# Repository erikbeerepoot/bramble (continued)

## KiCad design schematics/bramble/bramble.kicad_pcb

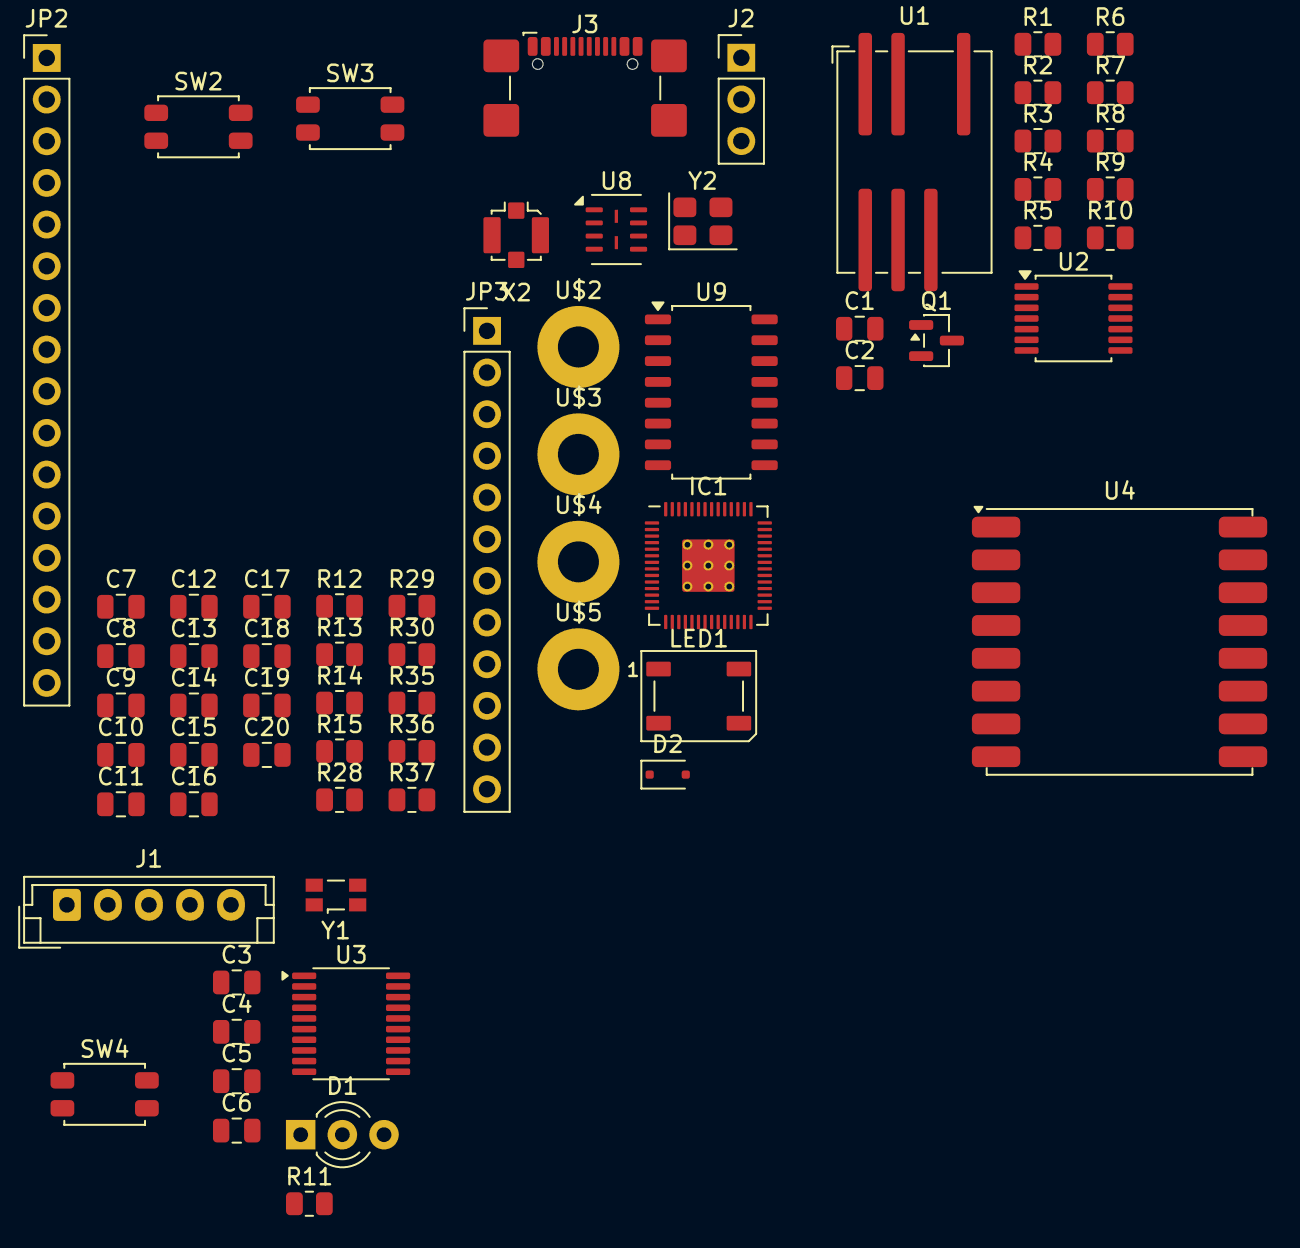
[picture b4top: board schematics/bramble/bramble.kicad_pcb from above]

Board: 2 copper layers, 67 parts (0 on the bottom side), 70 nets, no tracks yet.

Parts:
C1, C2: 10uF; C_0805_2012Metric
C3: 4.7uF; C_0805_2012Metric
C4, C5, C6: 100nF; C_0805_2012Metric
C7, C11, C12, C15, C17, C18, C19: 0.1uF; C_0805_2012Metric
C8, C13, C14, C16, C20: 1uF; C_0805_2012Metric
C9, C10: 22pF; C_0805_2012Metric
D1: LED_Dual_AKA; LED_D3.0mm-3
D2: 1N4148; D_SOD-323F
IC1: RP2040_QFN56; RP2040-QFN-56
J1: Conn_01x05_Pin; JST_EH_B5B-EH-A_1x05_P2.50mm_Vertical
J2: Conn_01x03; PinHeader_1x03_P2.54mm_Vertical
J3: USB_C_Receptacle_USB2.0_16P; USB_C_Receptacle_GCT_USB4110
JP2: HEADER-1X16ROUND; PinHeader_1x16_P2.54mm_Vertical
JP3: HEADER-1X12; PinHeader_1x12_P2.54mm_Vertical
LED1: WS2812B_SK6805_1515; LED_WS2812B_PLCC4_5.0x5.0mm_P3.2mm
Q1: DMN3300U; SOT-23
R1, R4: 100; R_0805_2012Metric
R2, R7, R11: 10k; R_0805_2012Metric
R3, R5, R8: 1k; R_0805_2012Metric
R6: 0.1; R_0805_2012Metric
R9: 20k; R_0805_2012Metric
R10: 8.2k; R_0805_2012Metric
R12, R13: 5.1K; R_0805_2012Metric
R14, R15: 22 ohm; R_0805_2012Metric
R28, R35, R36, R37: 10K; R_0805_2012Metric
R29, R30: 1K; R_0805_2012Metric
SW2, SW3, SW4: SW_MEC_5E; SW_SPST_EVQP2_MiddlePushTravel_H2.5mm
U1: TDN_5-0910WISM; Converter_DCDC_TRACO_TDN_5-xxxxWISM_SMD
U2: Opamp_Quad; TSSOP-14_4.4x5mm_P0.65mm
U3: STM32L010F4P6; TSSOP-20_4.4x6.5mm_P0.65mm
U4: RFM95W-915S2; HOPERF_RFM9XW_SMD
U8: 8MB QSPI; Winbond_USON-8-2EP_3x4mm_P0.8mm_EP0.2x0.8mm
U9: MT25QL01GBBB8ESF-0SIT; SOP-16_4.55x10.3mm_P1.27mm
U$2, U$3, U$4, U$5: MOUNTINGHOLE2.5; MountingHole_2.5mm_Pad
X2: uFL; U.FL_Molex_MCRF_73412-0110_Vertical
Y1: SG-3030CM; Oscillator_SMD_SeikoEpson_SG3030CM
Y2: 12Mhz; Crystal_SMD_Abracon_ABM8G-4Pin_3.2x2.5mm

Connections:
1.2V: C7.2, C8.1, C11.2, C12.2, IC1.23 (DVDD), IC1.45 (VREG_VOUT), IC1.50 (DVDD)
+3.3V: C1.1, C2.1, C3.1, C4.1, C5.1, U1.7 (+VOUT), U2.4 (V+)
+3V3: C13.1, C14.1, C15.1, C16.1, C17.1, C18.1, C19.1, C20.1, IC1.1 (IOVDD), IC1.10 (IOVDD), IC1.22 (IOVDD), IC1.33 (IOVDD), IC1.42 (IOVDD), IC1.43 (ADC_IOVDD), IC1.44 (VREG_IOVDD), IC1.48 (USB_IOVDD), IC1.49 (IOVDD), JP2.14, JP2.15, LED1.2 (VDD), R28.1, R35.2, R36.2, R37.2, U4.13 (3.3V), U8.8 (VCC), U9.2 (VCC)
+9V: Q1.2 (S), R9.2
/RP2040_ADC_2: U2.6 (-), U2.7
/pmu/NRST: C6.2, J1.4, SW4.1, SW4.2, U3.4 (NRST)
/rp2040/A0: IC1.38 (GPIO26/AD0), JP2.12
/rp2040/A1: IC1.39 (GPIO27/AD1), JP2.11
/rp2040/A2: IC1.40 (GPIO28/AD2), JP2.10
/rp2040/A3: IC1.41 (GPIO29/AD3), JP2.9
/rp2040/D4: IC1.6 (GPIO4), LED1.1 (DI)
/rp2040/D5: IC1.7 (GPIO5), JP3.10
/rp2040/D6: IC1.8 (GPIO6), JP3.9
/rp2040/D9: IC1.12 (GPIO9), JP3.8
/rp2040/D10: IC1.13 (GPIO10), JP3.7
/rp2040/D11: IC1.14 (GPIO11), JP3.6
/rp2040/D24: IC1.36 (GPIO24), JP2.8
/rp2040/D25: IC1.37 (GPIO25), JP2.7
/rp2040/D+: IC1.47 (USB_D+), R15.2
/rp2040/D-: IC1.46 (USB_D-), R14.2
/rp2040/MISO: IC1.11 (GPIO8), JP2.4, U4.2 (MISO)
/rp2040/MOSI: IC1.18 (GPIO15), JP2.5, U4.3 (MOSI)
/rp2040/QSPI_CS: IC1.56 (~QSPI_CS), R30.1
/rp2040/RFM_CS: IC1.27 (GPIO16), R36.1, U4.5 (NSS)
/rp2040/RFM_IO0: IC1.32 (GPIO21), U4.14 (DIO0)
/rp2040/RFM_IO1: IC1.34 (GPIO22), U4.15 (DIO1)
/rp2040/RFM_IO2: IC1.35 (GPIO23), U4.16 (DIO2)
/rp2040/RFM_IO3: IC1.30 (GPIO19), U4.11 (DIO3)
/rp2040/RFM_IO4: IC1.31 (GPIO20), U4.12 (DIO4)
/rp2040/RFM_IO5: IC1.29 (GPIO18), U4.7 (DIO5)
/rp2040/RFM_RST: IC1.28 (GPIO17), R35.1, U4.6 (RESET)
/rp2040/RX: IC1.3 (GPIO1), JP2.3
/rp2040/SCK: IC1.17 (GPIO14), JP2.6, U4.4 (SCK)
/rp2040/SCL: IC1.5 (GPIO3), JP3.11
/rp2040/SDA: IC1.4 (GPIO2), JP3.12
/rp2040/SWCLK: IC1.24 (SWCLK), J2.1
/rp2040/SWDIO: IC1.25 (SWDIO), J2.2
/rp2040/TX: IC1.2 (GPIO0), JP2.2
/rp2040/USBBOOT: IC1.9 (GPIO7), SW2.1, SW2.2
/rp2040/cs: R37.1, U8.1 (SSEL)
/rp2040/d0: U8.5 (MOSI), U9.15 (DQ0)
/rp2040/d1: U8.2 (MISO), U9.8 (DQ1)
/rp2040/d2: U8.3 (WP#/IO2), U9.9 (W#/DQ2)
/rp2040/d3: U8.7 (HOLD#/IO3), U9.1 (DQ3/HOLD#)
/rp2040/sck: U8.6 (SCK), U9.16 (C)
/rp2040/~RESET: IC1.26 (/RUN), JP2.16, R28.2, SW3.1, SW3.2
GND: C1.2, C2.2, C3.2, C4.2, C5.2, C6.1, C7.1, C8.2, C9.1, C10.1, C11.1, C12.1, C13.2, C14.2, C15.2, C16.2, C17.2, C18.2, C19.2, C20.2, D1.2 (K), IC1.19 (TESTEN), IC1.57 (GND), J1.5, J2.3, J3.A1 (GND), J3.A12 (GND), J3.B1 (GND), J3.B12 (GND), JP2.1, JP2.13, LED1.4 (GND), R2.2, R4.2, R5.1, R6.1, R10.1, R11.2, R12.1, R13.1, U1.2 (-VIN), U2.11 (V-), U3.15 (VSS), U4.1 (GND), U4.8 (GND), U4.10 (GND), U8.4 (VSS), U9.10 (VSS), X2.1 (GND@0), X2.2 (GND@1), Y1.2 (GND)
GNDPWR: R3.2, R6.2
unnamed: C10.2, R29.1, Y2.1
unnamed: D1.1 (A1), U3.10 (PA4)
unnamed: D1.3 (A2), U3.11 (PA5)
unnamed: C9.2, IC1.20 (XIN), Y2.2
unnamed: IC1.21 (XOUT), R29.2
unnamed: J1.2, U3.20 (PA14)
unnamed: J1.3, U3.19 (PA13)
unnamed: J3.A5 (CC1), R13.2
unnamed: J3.B5 (CC2), R12.2
unnamed: J3.A6 (D+), R14.1
unnamed: J3.A7 (D-), R15.1
unnamed: Q1.3 (D), U1.1 (+VIN)
unnamed: Q1.1 (G), R1.1, R2.1
unnamed: R7.2, R8.2, U2.1
unnamed: R3.1, R4.1, U2.3 (+)
unnamed: R5.2, R7.1, U2.2 (-)
unnamed: R9.1, R10.2, U2.5 (+)
unnamed: R11.1, U3.1 (PB9-BOOT0)
unnamed: U3.2 (PC14-OSC32_IN), Y1.1 (VIO)
unnamed: U3.3 (PC15-OSC32_OUT), Y1.3 (OUT)
STM32_SUPPLY: J1.1, U3.5 (VDDA), U3.16 (VDD), Y1.4 (Vcc)
VBUS: IC1.16 (GPIO13), J3.A4 (VBUS), J3.A9 (VBUS), J3.B4 (VBUS), J3.B9 (VBUS)

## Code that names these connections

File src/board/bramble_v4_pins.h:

#pragma once

/**
 * @file bramble_v4_pins.h
 * @brief Pin definitions for Bramble v4 board (custom RP2350B)
 *
 * Physical headers define the GPIO-to-connector mapping. Functional constants
 * reference header pins so the relationship between schematic, PCB, and code
 * is explicit.
 *
 * NOTE: J7 PCB silkscreen labels use v3-era numbering (GPIO28-31) but the
 *       actual RP2350B GPIOs are 36-39. The namespaces below use the real
 *       GPIO numbers.
 */

#include "hardware/i2c.h"
#include "hardware/spi.h"
#include "hardware/uart.h"

namespace Board {

// ==========================================================================
// Physical header definitions (GPIO numbers for each connector pin)
// Pin 1 = +3V3, Pin 2 = +9V, Pin 11 = VDD, Pin 12 = GND on all headers
// ==========================================================================

namespace J6 {                  // Motor/Valve connector (GPIO 28-35)
constexpr uint8_t PIN_3 = 35;   // VALVE_3
constexpr uint8_t PIN_4 = 34;   // MOTOR_LO_2
constexpr uint8_t PIN_5 = 33;   // VALVE_4
constexpr uint8_t PIN_6 = 32;   // MOTOR_LO_1
constexpr uint8_t PIN_7 = 31;   // VALVE_2
constexpr uint8_t PIN_8 = 30;   // MOTOR_HI_2
constexpr uint8_t PIN_9 = 29;   // VALVE_1
constexpr uint8_t PIN_10 = 28;  // MOTOR_HI_1
}  // namespace J6

namespace J7 {  // GPIO/debug header (GPIO 36-43)
// PCB silkscreen uses v3 numbering — real RP2350B GPIOs listed here
constexpr uint8_t PIN_3 = 43;   // labeled GPIO43_ADC3
constexpr uint8_t PIN_4 = 42;   // labeled GPIO42_ADC2
constexpr uint8_t PIN_5 = 41;   // labeled GPIO41_ADC1
constexpr uint8_t PIN_6 = 40;   // labeled GPIO40_ADC0
constexpr uint8_t PIN_7 = 39;   // labeled GPIO31
constexpr uint8_t PIN_8 = 38;   // labeled GPIO30
constexpr uint8_t PIN_9 = 37;   // labeled GPIO29
constexpr uint8_t PIN_10 = 36;  // labeled GPIO28
}  // namespace J7

namespace J8 {  // General purpose header (GPIO 20-27)
constexpr uint8_t PIN_3 = 26;
constexpr uint8_t PIN_4 = 27;
constexpr uint8_t PIN_5 = 24;
constexpr uint8_t PIN_6 = 25;
constexpr uint8_t PIN_7 = 22;
constexpr uint8_t PIN_8 = 23;
constexpr uint8_t PIN_9 = 20;
constexpr uint8_t PIN_10 = 21;
}  // namespace J8

// ==========================================================================
// Functional pin assignments (reference header pins)
// ==========================================================================

// --- LoRa (SX1262 / NiceRF LORA1262 on SPI1) ---
// NOTE: MOSI/SCK swapped vs RP2350 pin mux — needs bit-bang SPI
// DIO1 and BUSY need bodge wire to RFM_IO pads
inline auto LORA_SPI_PORT = spi1;
constexpr uint LORA_PIN_MISO = 12;
constexpr uint LORA_PIN_MOSI = 14;  // PCB trace to SX1262 MOSI (RP2350 pin mux = SPI1 SCK)
constexpr uint LORA_PIN_SCK = 15;   // PCB trace to SX1262 SCK  (RP2350 pin mux = SPI1 TX)
constexpr uint LORA_PIN_CS = 10;
constexpr uint LORA_PIN_RST = 16;
constexpr uint LORA_PIN_DIO1 = 19;  // DIO1 bodge wire → GPIO19
constexpr uint LORA_PIN_BUSY = 17;  // BUSY bodge wire → GPIO17

// --- External flash (dedicated SPI0) ---
constexpr bool FLASH_HAS_DEDICATED_SPI = true;
inline auto FLASH_SPI_PORT = spi0;
constexpr uint FLASH_PIN_MISO = 0;
constexpr uint FLASH_PIN_SCK = 2;
constexpr uint FLASH_PIN_MOSI = 3;
constexpr uint FLASH_PIN_CS = 1;
constexpr uint FLASH_PIN_RST = 5;

// --- QSPI flash size (on-board) ---
constexpr uint32_t QSPI_FLASH_SIZE = 2 * 1024 * 1024;  // 2MB (W25Q16JV)

// --- NeoPixel ---
constexpr uint PIN_NEOPIXEL = 4;

// --- I2C (sensors) --- (J8 pins 3/4)
inline auto SENSOR_I2C_PORT = i2c1;
constexpr uint PIN_I2C_SDA = J8::PIN_3;  // GPIO 26
constexpr uint PIN_I2C_SCL = J8::PIN_4;  // GPIO 27

// --- Analog/digital inputs ---
constexpr uint PIN_A0 = J8::PIN_3;  // GPIO 26
constexpr uint PIN_A1 = J8::PIN_4;  // GPIO 27

// --- PMU UART (UART1 on GPIO8/9) ---
inline auto PMU_UART_PORT = uart1;
constexpr uint PMU_UART_TX_PIN = 8;
constexpr uint PMU_UART_RX_PIN = 9;

// --- Default stdio UART (UART0 on J6 header — no conflict with PMU on UART1) ---
constexpr int DEFAULT_UART = 0;
constexpr int DEFAULT_UART_TX_PIN = J6::PIN_10;  // GPIO 28 (UART0 TX)
constexpr int DEFAULT_UART_RX_PIN = J6::PIN_9;   // GPIO 29 (UART0 RX)

// --- API UART (hub ↔ Raspberry Pi / CM5) — UART0 on J6 (stdio is on USB CDC) ---
inline auto API_UART_PORT = uart0;
constexpr uint API_UART_TX_PIN = J6::PIN_10;  // GPIO 28
constexpr uint API_UART_RX_PIN = J6::PIN_9;   // GPIO 29

// --- Valve / Motor pins (J7 header) ---
// Valve connector plugs into J7 instead of J6 to free J6 for UART0.
// H-bridge pins are always defined (DC latching path; unused in an AC build,
// where GPIO36/38 instead drive the two AC SSR gates directly).
constexpr uint8_t PIN_MOTOR_HI_1 = J7::PIN_10;  // GPIO 36
constexpr uint8_t PIN_MOTOR_HI_2 = J7::PIN_8;   // GPIO 38
constexpr uint8_t PIN_MOTOR_LO_1 = J7::PIN_6;   // GPIO 40
constexpr uint8_t PIN_MOTOR_LO_2 = J7::PIN_4;   // GPIO 42

#ifdef HARDWARE_IRRIGATION_AC
// AC variant: two AC valves switched by SSRs on GPIO36/38 (the H-bridge HI
// pins, repurposed as direct SSR gates). No indexer.
constexpr uint8_t NUM_VALVES = 2;
constexpr uint8_t VALVE_PINS[NUM_VALVES] = {
    36,  // VALVE_1 = SSR gate, silicon GPIO36
    38,  // VALVE_2 = SSR gate, silicon GPIO38
};
#else
constexpr uint8_t NUM_VALVES = 4;
// IMPORTANT: these are *silicon* GPIO numbers (what gpio_put() drives), NOT the
// schematic net labels. The RP2350B sheet names these nets "GPIO37/39/43/41",
// but those nets physically land on pads GPIO29/31/41/43 — verified against the
// pad column in rp2040.kicad_sch and on the bench. Using the net-label numbers
// (the old J7 aliases) left VALVE_2 driving an unconnected pin, and swapped
// VALVE_3/VALVE_4.
constexpr uint8_t VALVE_PINS[NUM_VALVES] = {
    29,  // VALVE_1 = silicon GPIO29
    31,  // VALVE_2 = silicon GPIO31
    41,  // VALVE_3 = silicon GPIO41
    43,  // VALVE_4 = silicon GPIO43
};
#endif

// --- Curtain motor pins (greenhouse variant, J7 header) ---
// Relay-based motor reversing: one GPIO per direction
// Silkscreen labels GPIO31/GPIO30 (v3 numbering); real RP2350B GPIOs are 39/38
constexpr uint8_t PIN_CURTAIN_OPEN = J7::PIN_6;   // J7 pin 6 → GPIO 40
constexpr uint8_t PIN_CURTAIN_CLOSE = J7::PIN_8;  // J7 pin 8 → GPIO 38

}  // namespace Board

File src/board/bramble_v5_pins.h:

#pragma once

/**
 * @file bramble_v5_pins.h
 * @brief Pin definitions for Bramble v5 board (custom RP2350B)
 *
 * v5 fixes the v4 PCB wiring defects:
 *   - LoRa MOSI/SCK no longer swapped — hardware SPI1 works directly
 *   - SX1262 DIO1 / BUSY routed natively (no bodge wires)
 *   - PMU UART RX on GPIO9 functional (no bodge to GPIO21)
 */

#include "hardware/i2c.h"
#include "hardware/spi.h"
#include "hardware/uart.h"

namespace Board {

// ==========================================================================
// Physical header definitions (GPIO numbers for each connector pin)
// Pin 1 = +3V3, Pin 2 = +9V, Pin 11 = VDD, Pin 12 = GND on all headers
// ==========================================================================

namespace J6 {                  // Motor/Valve connector (GPIO 28-35)
constexpr uint8_t PIN_3 = 35;   // VALVE_3
constexpr uint8_t PIN_4 = 34;   // MOTOR_LO_2
constexpr uint8_t PIN_5 = 33;   // VALVE_4
constexpr uint8_t PIN_6 = 32;   // MOTOR_LO_1
constexpr uint8_t PIN_7 = 31;   // VALVE_2
constexpr uint8_t PIN_8 = 30;   // MOTOR_HI_2
constexpr uint8_t PIN_9 = 29;   // VALVE_1
constexpr uint8_t PIN_10 = 28;  // MOTOR_HI_1
}  // namespace J6

namespace J7 {  // GPIO/debug header (GPIO 36-43)
constexpr uint8_t PIN_3 = 43;
constexpr uint8_t PIN_4 = 42;
constexpr uint8_t PIN_5 = 41;
constexpr uint8_t PIN_6 = 40;
constexpr uint8_t PIN_7 = 39;
constexpr uint8_t PIN_8 = 38;
constexpr uint8_t PIN_9 = 37;
constexpr uint8_t PIN_10 = 36;
}  // namespace J7

namespace J8 {  // General purpose header (GPIO 20-27)
constexpr uint8_t PIN_3 = 26;
constexpr uint8_t PIN_4 = 27;
constexpr uint8_t PIN_5 = 24;
constexpr uint8_t PIN_6 = 25;
constexpr uint8_t PIN_7 = 22;
constexpr uint8_t PIN_8 = 23;
constexpr uint8_t PIN_9 = 20;
constexpr uint8_t PIN_10 = 21;
}  // namespace J8

// ==========================================================================
// Functional pin assignments
// ==========================================================================

// --- LoRa (SX1262 / NiceRF LORA1262 on hardware SPI1) ---
// v5: PCB routes MOSI to GPIO15 and SCK to GPIO14 — matches SPI1 pin mux,
// so hardware SPI works directly (no bit-bang needed unlike v4).
inline auto LORA_SPI_PORT = spi1;
constexpr uint LORA_PIN_MISO = 12;  // SPI1 RX
constexpr uint LORA_PIN_SCK = 14;   // SPI1 SCK
constexpr uint LORA_PIN_MOSI = 15;  // SPI1 TX
constexpr uint LORA_PIN_CS = 10;    // GPIO chip-select (not hardware CSn)
constexpr uint LORA_PIN_RST = 16;
constexpr uint LORA_PIN_DIO1 = 19;
constexpr uint LORA_PIN_BUSY = 18;

// --- External flash (dedicated SPI0) ---
constexpr bool FLASH_HAS_DEDICATED_SPI = true;
inline auto FLASH_SPI_PORT = spi0;
constexpr uint FLASH_PIN_MISO = 0;
constexpr uint FLASH_PIN_SCK = 2;
constexpr uint FLASH_PIN_MOSI = 3;
constexpr uint FLASH_PIN_CS = 1;
constexpr uint FLASH_PIN_RST = 5;

// --- QSPI flash size (on-board) ---
constexpr uint32_t QSPI_FLASH_SIZE = 2 * 1024 * 1024;  // 2MB (W25Q16JV)

// --- NeoPixel ---
constexpr uint PIN_NEOPIXEL = 4;

// --- I2C (sensors) --- (J8 pins 3/4)
inline auto SENSOR_I2C_PORT = i2c1;
constexpr uint PIN_I2C_SDA = J8::PIN_3;  // GPIO 26
constexpr uint PIN_I2C_SCL = J8::PIN_4;  // GPIO 27

// --- Analog/digital inputs ---
constexpr uint PIN_A0 = J8::PIN_3;  // GPIO 26
constexpr uint PIN_A1 = J8::PIN_4;  // GPIO 27

// --- PMU UART (UART1 on GPIO8/9) ---
inline auto PMU_UART_PORT = uart1;
constexpr uint PMU_UART_TX_PIN = 8;
constexpr uint PMU_UART_RX_PIN = 9;

// --- Default stdio UART (UART0 on J6 header — no conflict with PMU on UART1) ---
constexpr int DEFAULT_UART = 0;
constexpr int DEFAULT_UART_TX_PIN = J6::PIN_10;  // GPIO 28 (UART0 TX)
constexpr int DEFAULT_UART_RX_PIN = J6::PIN_9;   // GPIO 29 (UART0 RX)

// --- API UART (hub ↔ Raspberry Pi / CM5) — UART0 on J6 (stdio is on USB CDC) ---
inline auto API_UART_PORT = uart0;
constexpr uint API_UART_TX_PIN = J6::PIN_10;  // GPIO 28
constexpr uint API_UART_RX_PIN = J6::PIN_9;   // GPIO 29

// --- Valve / Motor pins (J7 header) ---
// H-bridge pins are always defined (used by the DC latching path; unused in an
// AC build, where GPIO36/38 instead drive the two AC SSR gates directly).
constexpr uint8_t PIN_MOTOR_HI_1 = J7::PIN_10;  // GPIO 36
constexpr uint8_t PIN_MOTOR_HI_2 = J7::PIN_8;   // GPIO 38
constexpr uint8_t PIN_MOTOR_LO_1 = J7::PIN_6;   // GPIO 40
constexpr uint8_t PIN_MOTOR_LO_2 = J7::PIN_4;   // GPIO 42

#ifdef HARDWARE_IRRIGATION_AC
// AC variant: two AC valves switched by SSRs on GPIO36/38 (the H-bridge HI
// pins, repurposed as direct SSR gates). No indexer.
constexpr uint8_t NUM_VALVES = 2;
constexpr uint8_t VALVE_PINS[NUM_VALVES] = {
    36,  // VALVE_1 = SSR gate, silicon GPIO36
    38,  // VALVE_2 = SSR gate, silicon GPIO38
};
#else
constexpr uint8_t NUM_VALVES = 4;
// IMPORTANT: these are *silicon* GPIO numbers (what gpio_put() drives), NOT the
// schematic net labels. The RP2350B sheet names these nets "GPIO37/39/43/41",
// but those nets physically land on pads GPIO29/31/41/43 — verified against the
// pad column in rp2040.kicad_sch and on the bench. Using the net-label numbers
// (the old J7 aliases) left VALVE_2 driving an unconnected pin, and swapped
// VALVE_3/VALVE_4.
constexpr uint8_t VALVE_PINS[NUM_VALVES] = {
    37,  // VALVE_1 = silicon GPIO37
    39,  // VALVE_2 = silicon GPIO39
    41,  // VALVE_3 = silicon GPIO41
    43,  // VALVE_4 = silicon GPIO43
};
#endif

// --- Curtain motor pins (greenhouse variant, J7 header) ---
constexpr uint8_t PIN_CURTAIN_OPEN = J7::PIN_6;   // GPIO 40
constexpr uint8_t PIN_CURTAIN_CLOSE = J7::PIN_8;  // GPIO 38

}  // namespace Board

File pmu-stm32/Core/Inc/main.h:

/* USER CODE BEGIN Header */
/**
  ******************************************************************************
  * @file           : main.h
  * @brief          : Header for main.c file.
  *                   This file contains the common defines of the application.
  ******************************************************************************
  * @attention
  *
  * <h2><center>&copy; Copyright (c) 2025 STMicroelectronics.
  * All rights reserved.</center></h2>
  *
  * This software component is licensed by ST under BSD 3-Clause license,
  * the "License"; You may not use this file except in compliance with the
  * License. You may obtain a copy of the License at:
  *                        opensource.org/licenses/BSD-3-Clause
  *
  ******************************************************************************
  */
/* USER CODE END Header */

/* Define to prevent recursive inclusion -------------------------------------*/
#ifndef __MAIN_H
#define __MAIN_H

#ifdef __cplusplus
extern "C" {
#endif

/* Includes ------------------------------------------------------------------*/
#include "stm32l0xx_hal.h"

/* Private includes ----------------------------------------------------------*/
/* USER CODE BEGIN Includes */

/* USER CODE END Includes */

/* Exported types ------------------------------------------------------------*/
/* USER CODE BEGIN ET */

/* USER CODE END ET */

/* Exported constants --------------------------------------------------------*/
/* USER CODE BEGIN EC */

/* USER CODE END EC */

/* Exported macro ------------------------------------------------------------*/
/* USER CODE BEGIN EM */

/* USER CODE END EM */

/* Exported functions prototypes ---------------------------------------------*/
void Error_Handler(void);

/* USER CODE BEGIN EFP */

/* USER CODE END EFP */

/* Private defines -----------------------------------------------------------*/

/* USER CODE BEGIN Private defines */

// Pin definitions for Bramble PMU
#define WAKE_BUTTON_PIN     GPIO_PIN_0  // PA0, pin 6 - Wake button (active high, ext. pull-down)
#define DCDC_EN_PIN         GPIO_PIN_1  // PA1, pin 7 - DC/DC converter enable
#define LED_RED_PIN         GPIO_PIN_4  // PA4, pin 10 - Red LED
#define LED_GREEN_PIN       GPIO_PIN_5  // PA5, pin 11 - Green LED

// I2C1 pins for FRAM (FM24CL16B-GTR)
#define FRAM_SCL_PIN        GPIO_PIN_9  // PA9, pin 17 - I2C1 SCL
#define FRAM_SDA_PIN        GPIO_PIN_10 // PA10, pin 18 - I2C1 SDA

/* USER CODE END Private defines */

#ifdef __cplusplus
}
#endif

#endif /* __MAIN_H */

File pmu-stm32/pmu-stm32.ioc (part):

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Mcu.Name=STM32L010F4Px
Mcu.Package=TSSOP20
Mcu.UserName=STM32L010F4Px
PA1.Signal=GPIO_Output
PA2.Mode=Asynchronous
PA2.Signal=LPUART1_TX
PA3.Mode=Asynchronous
PA3.Signal=LPUART1_RX
PA4.Signal=GPIO_Output
PA5.Signal=GPIO_Output
RCC.HSE_VALUE=8000000
RCC.SYSCLKFreq_VALUE=2097000
board=custom

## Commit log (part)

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2026-03-25 style: auto-format code with clang-format
2026-03-25 refactor(flash): remove stale V3 shared-SPI references from comments and logs
    V4 has a dedicated SPI0 bus for external flash, so references to
    shared SPI1/LoRa bus contention no longer apply. Remove hardcoded
    GPIO numbers from struct field comments since pins are configurable.
2026-03-25 fix(v4): deselect flash CS and RST before SPI init to prevent bad state
    Flash CS can float low on power-up, causing the flash to interpret SPI
    initialization traffic as commands and become unresponsive. Deselect CS
    and deassert RST before calling spi_init(), matching the V3 pattern.
    Also use Board::FLASH_SPI_PORT instead of hardcoded spi0.
2026-03-25 fix(flash): increase post-reset recovery delay from 10ms to 30ms
    The MT25QL spec allows up to 10ms for tPUW (power-up to first command).
    Using exactly the spec maximum left zero margin, which could cause
    intermittent init failures. Increase to 30ms for 3x safety margin.
2026-03-26 fix(flash): remove unnecessary wakeUp() call after hardware reset
    Hardware reset already exits deep power-down mode (per MT25QL datasheet
    p66). Sending 0xAB (RELEASE_POWER_DOWN) after reset is redundant and
    may contribute to init failures requiring multiple retry attempts.
2026-03-29 feat(hub): add SEND_ACTUATOR command and greenhouse node detection
    Add SEND_ACTUATOR serial command to forward actuator commands over LoRa
    to greenhouse nodes with RELIABLE delivery. Update LIST_NODES to detect
    greenhouse nodes via node_type instead of capabilities alone.
2026-03-29 feat(hal): add interactive calibration state machine to curtain controller
    Implement multi-phase calibration: CLOSING (full travel) -> PAUSE (1s)
    -> OPENING (user clicks stop when fully open). Records elapsed time as
    calibrated travel_time_ms. Includes CalibrationPhase enum and
    calibrationJustCompleted() poll method.
2026-03-29 feat(dashboard): add curtain control API endpoint and UI
    Add POST /api/nodes/<address>/curtain endpoint with open/close/stop
    actions, backed by queue_send_actuator in the command queue. Add
    CurtainControl component with three buttons rendered in NodeDetail
    for GREENHOUSE-type nodes. Add GREENHOUSE to NodeType constants.
2026-03-29 feat(greenhouse): persist travel time to flash and emit calibration event
    Add CurtainConfigManager for flash-backed travel time persistence with
    CRC32 verification and dual-sector backup. Load saved travel time on
    boot, handle CMD_CALIBRATE, persist after calibration completes, and
    send EVENT_CALIBRATION_COMPLETE with measured travel time.
2026-03-29 feat(lora): add MSG_TYPE_EVENT message type with hub forwarding
    Add generic event notification protocol with 2-byte event code and
    variable-length detail data. Includes EventPayload struct, message
    builder, validator update, ReliableMessenger::sendEvent(), and hub
    dispatch that forwards events to Raspberry Pi over UART as
    EVENT <addr> <device_id> <event_code> <data_hex>.
2026-03-29 feat(dashboard): add calibration button and guided calibration UI
    Add calibrate action to curtain API endpoint, calibration button with
    step-by-step status messages in CurtainControl component, and
    Calibration Complete event code display name.
2026-03-29 feat(api,dashboard): add event storage, API endpoint, and event history UI
    Add node_events table with insert/query methods, EVENT serial message
    parsing, GET /api/nodes/<device_id>/events endpoint, and event history
    display in CurtainControl component with event code name mapping.
2026-03-29 feat(greenhouse): emit events on curtain open/close/stop commands
2026-03-29 docs: note that VERSION file is managed by commit hook
2026-04-03 feat(greenhouse): add auto-detected temperature/humidity sensing
    Greenhouse node now probes for a CHT832X sensor on I2C at startup.
    If detected, reads every 60s and transmits via LoRa (batch size=1).
    Gracefully skips if no sensor is connected.
2026-04-04 plan: irrigation node detail page UI design
    Covers valve control (manual on/off), schedule management, and event
    history for the dashboard irrigation node detail view.
    https://claude.ai/code/session_01UdbUt1SDU7rTdYRNiT8VYY
2026-04-04 plan: replace manual on/off with run-once auto-off for irrigation
    Raw on/off risks leaving valves open. Run-once with duration presets
    (5m/15m/30m/custom) and automatic shutoff is safer and more practical.
    https://claude.ai/code/session_01UdbUt1SDU7rTdYRNiT8VYY
2026-04-04 plan: run-once via PMU schedule queue, stop button while running
    https://claude.ai/code/session_01UdbUt1SDU7rTdYRNiT8VYY
2026-04-06 fix(dashboard): restore sidebar layout on desktop for node detail
    Move Node Info, Node Status, and Advanced back into the left column div.
    Use order-first on the controls column for mobile priority instead of
    grid row placement which broke the desktop layout.
2026-04-06 feat(dashboard): reorder node detail sections for mobile
    Move Node Info, Node Status, and Advanced panels after the controls
    on small screens so users see actionable content first. Desktop
    layout unchanged via CSS grid ordering.
2026-04-06 feat(dashboard): redesign Run Once with duration chips and schedule drawer
    Replace the slider/select valve controls with horizontally scrollable
    duration chips (1-120min). Add vaul-based bottom sheet for Add Schedule
    with segmented valve selector, native time input, and circular day toggles.
    New dependencies: vaul (drawer), lucide-react (icons).
2026-04-06 feat(dashboard): responsive valve controls with native select on mobile
    Desktop keeps the slider row; mobile shows a stacked layout with a
    native <select> that renders as an iOS wheel picker. Fixes duration
    label showing "1.5h 30m" instead of "1h 30m".
2026-04-06 fix(dashboard): remove unused formatDurationLong function
    Fixes CI build failure from TS6133 (declared but never read).
2026-04-07 refactor: move generic update handling from IrrigationMode to ApplicationMode
    Move SET_WAKE_INTERVAL and SET_DATETIME handling into the base class so
    all battery-powered modes get update support without duplication.
    - Add UpdatePullState, ReliablePmuClient*, sendCheckUpdates() to ApplicationMode
    - Base onUpdateAvailable() handles protocol boilerplate and generic update types
    - Add virtual hooks: onModeSpecificUpdate, onUpdateApplied, onUpdateFailed, onUpdateReceived
    - IrrigationMode now only handles SET_SCHEDULE, REMOVE_SCHEDULE, ACTUATOR_COMMAND
2026-04-07 feat(sensor): add wake interval support to sensor nodes
    Wire SensorMode into the update pull protocol so sensor nodes can
    receive SET_WAKE_INTERVAL commands from the hub.
    - Expose ReliablePmuClient via SensorPmuManager::getReliablePmu()
    - Register PMU with base class in SensorMode::onStart()
    - Trigger CHECK_UPDATES on PENDING_FLAG_WAKE_INTERVAL in heartbeat
    - Override onUpdateApplied/onUpdateFailed for logging
2026-04-07 feat(dashboard): add wake interval control to node detail page
    Add UI for setting the wake interval on battery-powered nodes
    (sensor and irrigation) in the Advanced section of NodeDetail.
    - Add setWakeInterval() API client function
    - Add wake interval input (1-60 minutes) with status feedback
2026-04-07 refactor: extract keepAwake constant and update handler methods
    Pull hardcoded keepAwake(10) into KEEP_AWAKE_PROCESSING_SECONDS constant
    and extract handleSetWakeInterval/handleSetDatetime from onUpdateAvailable
    switch statement into separate methods.
2026-04-08 feat: add event log system with schedule confirmation
    Add an event logging system that records notable events on sensor and
    irrigation nodes, transmits them to the hub, and closes the loop on
    schedule delivery by confirming status back to the dashboard.
    New files:
    - event_record.h: EventType enum and 6-byte EventRecord struct
    - event_log.h: RAM ring buffer template for event accumulation
2026-04-08 feat(dashboard): add sensor sparkline to node cards
    Show last 6 hours of temperature data as a sparkline on sensor node
    cards. Two variants implemented to compare:
    - inline: clean SVG line chart below the temp/humidity readings
    - backdrop: semi-transparent area chart filling the card background
    Toggle via SPARKLINE_VARIANT constant in NodeCard.tsx (defaults to backdrop).
    https://claude.ai/code/session_01LwqVV3ADtuh2CuoKQ65Lqp
2026-04-11 feat(pmu): add generic blob storage to FRAM with SaveBlob/LoadBlob protocol
    Adds a reusable blob storage mechanism to PersistentStorage backed by
    FRAM. Slots are fixed-capacity regions identified by slot ID (slot 0 =
    node state reserve, slot 1 = event log). The STM32 treats blob data as
    opaque bytes.
    New protocol commands:
    - SaveBlob (0x1D): chunked write (36 bytes/msg), ACK'd per chunk
2026-04-11 fix(dashboard): replace Framer Motion with CSS animation for recent events
    Framer Motion's layout prop + AnimatePresence caused unreliable
    animations across browsers (especially Safari). Since the event list
    is loaded all at once, the motion overhead was unnecessary. Uses a
    CSS @keyframes fade-in with staggered delay instead.
2026-04-11 feat: emit missing event log entries for boot, sleep, and failure paths
    Adds event emissions for 6 defined-but-never-emitted EventTypes:
    - BOOT_COLD / BOOT_WATCHDOG in ApplicationMode::run() (all variants)
    - SLEEP_ENTER in ApplicationMode::onBeforeSleep() (all variants)
    - REGISTRATION_FAIL in SensorMode::attemptRegistration()
    - TIME_SYNC_TIMEOUT in SensorMode sync watchdog callback
    - TX_BATCH_FAIL in SensorMode::transmitBacklog() (both failure paths)
2026-04-11 feat: persist event log to FRAM when LoRa TX fails before sleep
    On the happy path (TX succeeds), no FRAM writes occur. When LoRa TX
    fails, remaining events are serialized and saved to FRAM blob slot 1
    via SaveBlob. On next wake, sensor and irrigation modes load persisted
    events back into the ring buffer for retransmission.
    ApplicationMode::onBeforeSleep now gates FRAM persistence on TX result.
    SensorPmuManager::loadPersistedEventLog loads blob on wake.
2026-04-11 feat: add RP2040 blob protocol client and EventLog persistence helpers
    Mirrors STM32 SaveBlob/LoadBlob/BlobData in the RP2040 protocol layer.
    Adds saveBlob/loadBlob/clearBlob to ReliablePmuClient with automatic
    chunking (36 bytes per message).
    Adds EventLog serialization methods (serializeToBlob, deserializeFromBlob,
    loadPersisted) for packing/unpacking event records to the blob format.
2026-04-26 docs: plan non-contiguous untransmitted sensor buffer
    Sketches demoting read_index to a scan-from hint and using a per-sector
    untransmitted-count summary in RAM (48KB on RP2350B) so the scanner can
    find untransmitted records efficiently even when they're sparsely
    distributed across the flash buffer.
    https://claude.ai/code/session_01PfZ5SiWkNPDNheEF5Vj1Rz
